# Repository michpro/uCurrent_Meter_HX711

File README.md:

# uCurrent Meter [HX711]

Nanoammeter based on Arduino and HX711 module.

# License

## Hardware
This hardware is licensed under CERN-OHL-P v2 or later.

Copyright © 2020 Michal Protasowicki

Source: https://github.com/michpro/uCurrent_Meter_HX711

This source describes Open Hardware and is licensed under the CERN-OHL-P v2
You may redistribute and modify this documentation and make products
using it under the terms of the CERN-OHL-P v2 or later (https:/cern.ch/cern-ohl).
This documentation is distributed WITHOUT ANY EXPRESS OR IMPLIED
WARRANTY, INCLUDING OF MERCHANTABILITY, SATISFACTORY QUALITY
AND FITNESS FOR A PARTICULAR PURPOSE. Please see the CERN-OHL-P v2
for applicable conditions

## Software
Software used in this project is released under ??? License.

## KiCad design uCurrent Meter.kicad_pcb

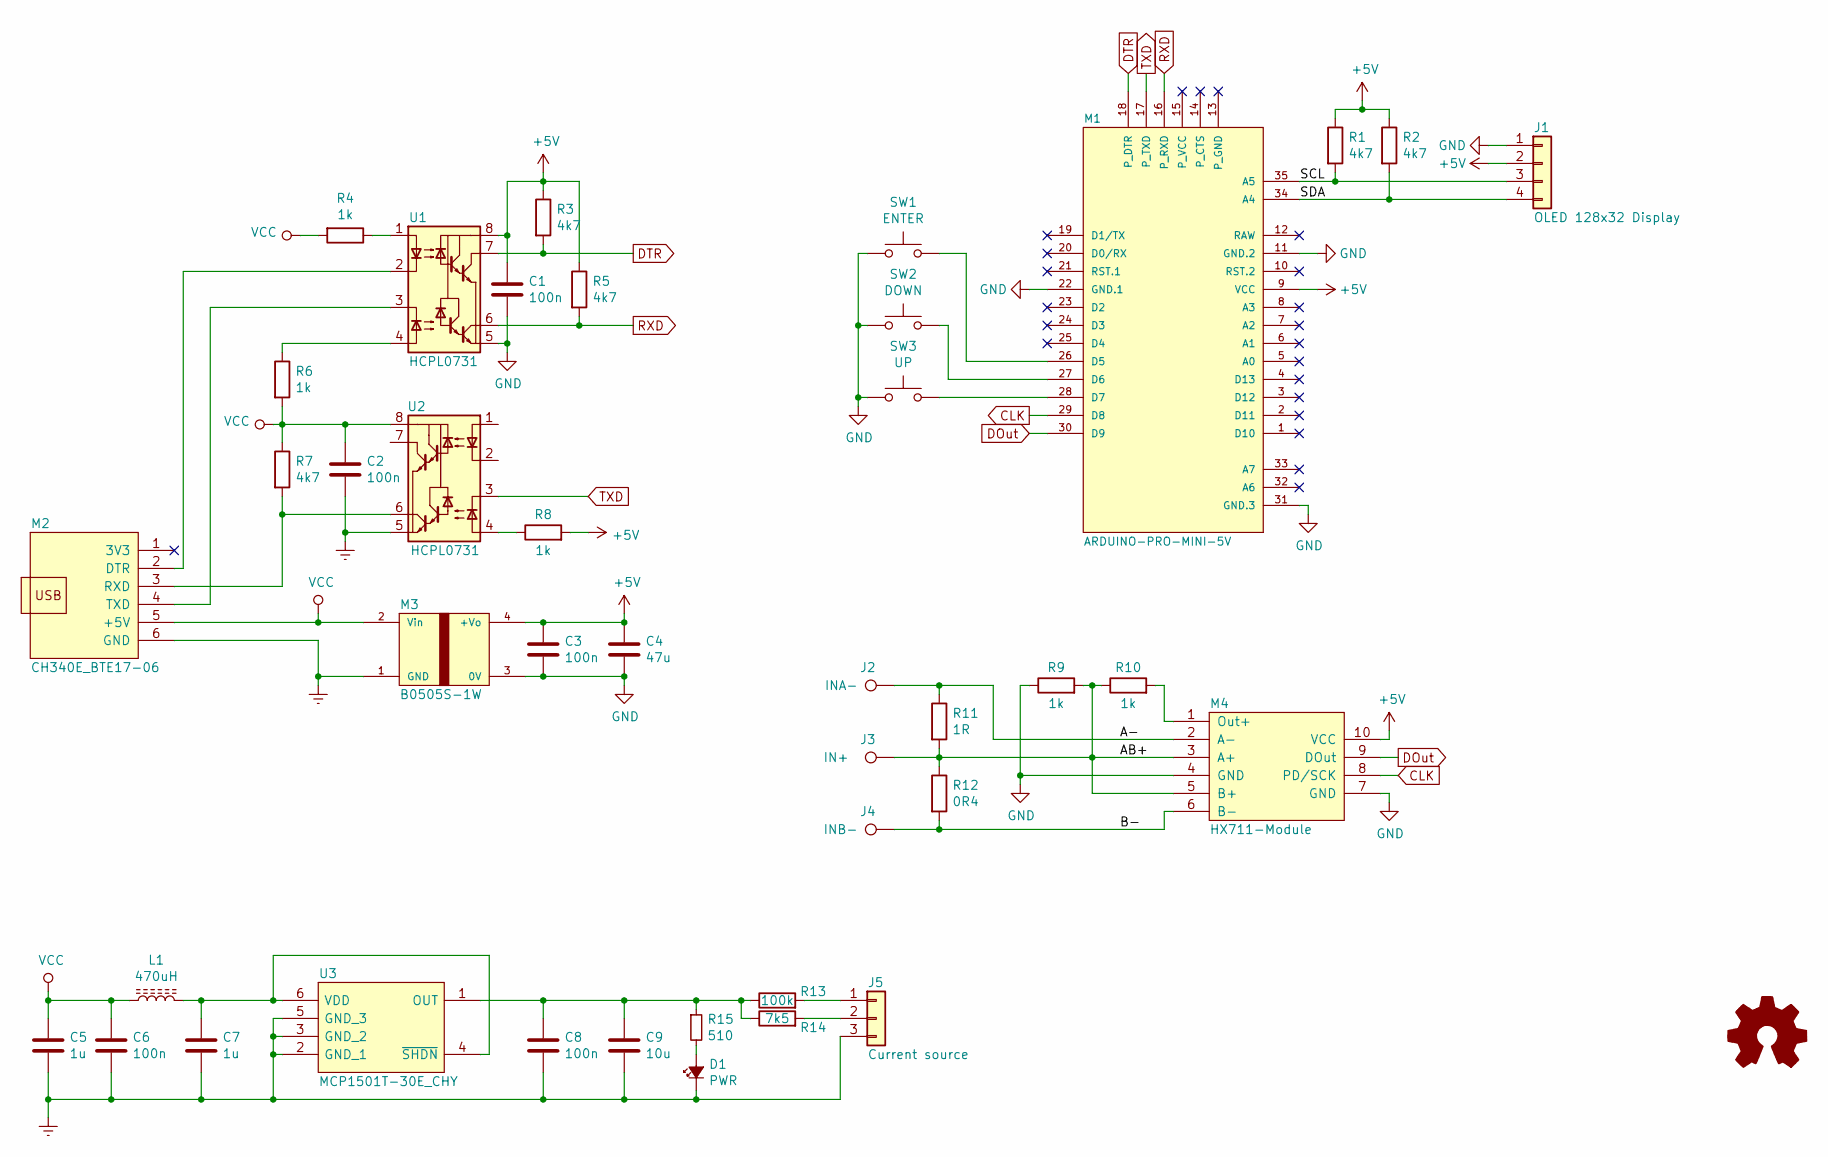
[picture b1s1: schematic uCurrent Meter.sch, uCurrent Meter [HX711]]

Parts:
C1, C2, C3, C6, C8: 100n; C_1206
C4: 47u; C_1206
C5, C7: 1u; C_1206
C9: 10u; C_1206
D1: PWR; D_1206
J1: OLED 128x32 Display; 128X32_OLED_I2C_0-91_inch
J2: INA-; MountingHole_2.2mm_M2_Pad
J3: IN+; MountingHole_2.2mm_M2_Pad
J4: INB-; MountingHole_2.2mm_M2_Pad
J5: Current source; CONN_3
L1: 470uH; L_Taiyo-Yuden_NR-60xx_HandSoldering
LOGO1: OPEN_HARDWARE_1
M1: ARDUINO-PRO-MINI-5V; diy-modules-ARDUINO-PRO-MINI
M2: CH340E_BTE17-06
M3: B0505S-1W; BxxyyS-1W
M4: HX711-Module
R1, R2, R3, R5, R7: 4k7; R_1206
R4, R6, R8, R9, R10: 1k; R_1206
R11: 1R; R_2512_HandSoldering
R12: 0R4; R_2512_HandSoldering
R13: 100k; R_MiniMELF_MMA-0204
R14: 7k5; R_MiniMELF_MMA-0204
R15: 510; R_1206
SW1: ENTER; SW_SPST_PTS645
SW2: DOWN; SW_SPST_PTS645
SW3: UP; SW_SPST_PTS645
U1, U2: HCPL0731; SO-8_5.3x6.2mm_Pitch1.27mm
U3: MCP1501T-30E_CHY; SOT-23-6; Manufacturer_Part_Number MCP1501T-10E/CHY

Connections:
+5V: C1.2, C3.1, C4.1, J1.2, M1.9 (VCC), M3.4 (+Vo), M4.10 (VCC), R1.1, R2.1, R3.1, R5.1, R8.2, U1.8 (VCC)
/SCL: J1.3, M1.35 (A5), R1.2
/SDA: J1.4, M1.34 (A4), R2.2
CLK: M1.29 (D8), M4.8 (PD/SCK)
DOut: M1.30 (D9), M4.9 (DOut)
DTR: M1.18 (P_DTR), R3.2, U1.7 (VO1)
Earth: C2.1, C5.2, C6.2, C7.2, C8.2, C9.2, D1.1 (K), J5.3, M2.6 (GND), M3.1 (GND), U2.5 (GND), U3.2 (GND_1), U3.3 (GND_2), U3.5 (GND_3)
GND: C1.1, C3.2, C4.2, J1.1, M1.11 (GND.2), M1.13 (P_GND), M1.14 (P_CTS), M1.22 (GND.1), M1.31 (GND.3), M3.3 (0V), M4.4 (GND), M4.7 (GND), R9.1, SW1.1, SW2.1, SW3.1, U1.5 (GND)
unnamed: C7.1, L1.2, U3.4 (~SHDN), U3.6 (VDD)
unnamed: C8.1, C9.1, R13.1, R14.1, R15.1, U3.1 (OUT)
unnamed: D1.2 (A), R15.2
unnamed: J2.1, M4.2 (A-), R11.1
unnamed: J3.1, M4.3 (A+), M4.5 (B+), R9.2, R10.1, R11.2, R12.1
unnamed: J4.1, M4.6 (B-), R12.2
unnamed: J5.1, R13.2
unnamed: J5.2, R14.2
unnamed: M1.26 (D5), SW1.2
unnamed: M1.27 (D6), SW2.2
unnamed: M1.28 (D7), SW3.2
unnamed: M2.2 (DTR), U1.2 (C1)
unnamed: M2.3 (RXD), R7.2, U2.6 (VO2)
unnamed: M2.4 (TXD), U1.3 (C2)
unnamed: M4.1 (Out+), R10.2
unnamed: R4.1, U1.1 (A1)
unnamed: R6.1, U1.4 (A2)
unnamed: R8.1, U2.4 (A2)
RXD: M1.16 (P_RXD), R5.2, U1.6 (VO2)
TXD: M1.17 (P_TXD), U2.3 (C2)
VCC: C2.2, C5.1, C6.1, L1.1, M2.5 (+5V), M3.2 (Vin), R4.2, R6.2, R7.1, U2.8 (VCC)

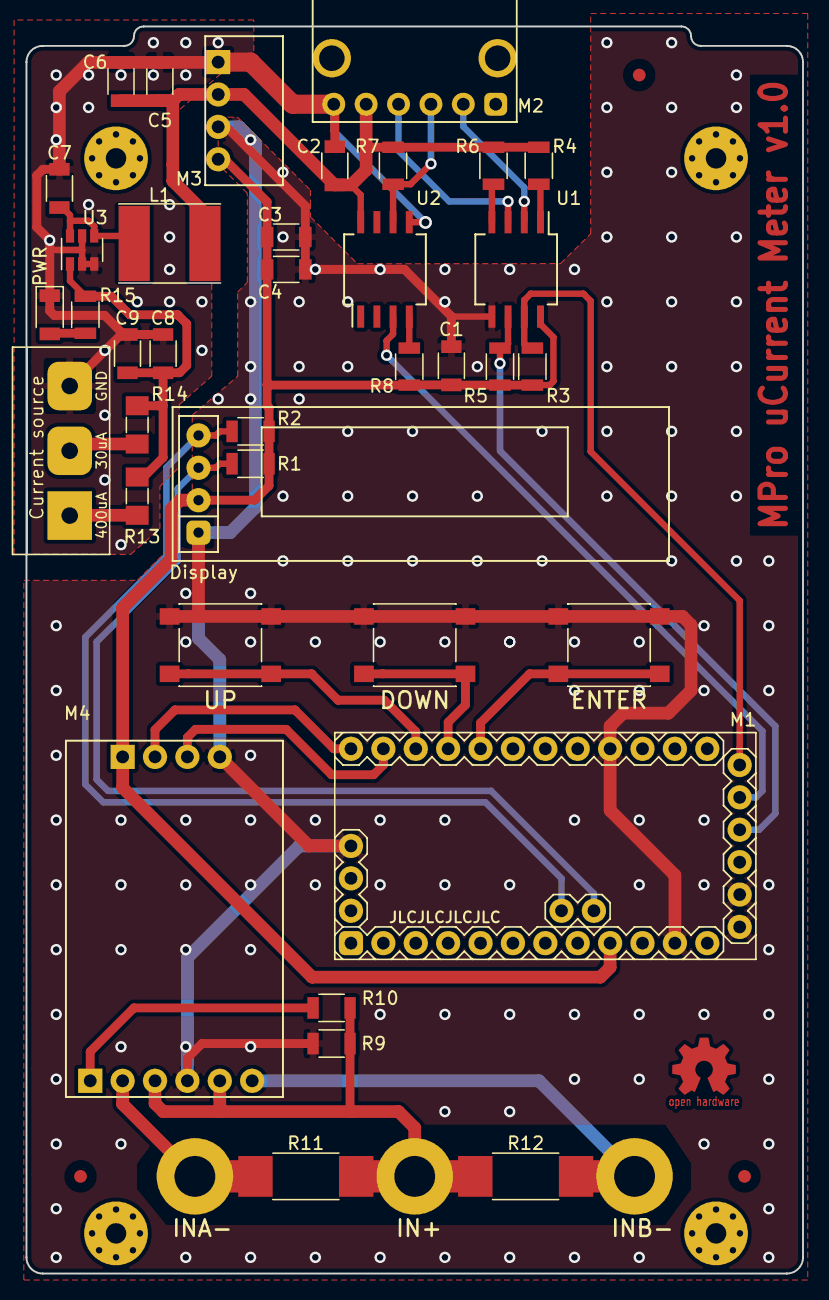
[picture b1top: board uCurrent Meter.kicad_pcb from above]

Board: 2 copper layers, 60.9 x 97.8 mm, 41 parts (0 on the bottom side), 29 nets.

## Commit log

2021-04-17 first hardware revision
2021-04-18 added datasheets to documentation

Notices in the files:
README.md:
License: CERN-OHL-P v2
uCurrent Meter.sch:
Copyright © 2020 by Michal Protasowicki
